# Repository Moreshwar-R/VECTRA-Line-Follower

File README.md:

# 🏁 VECTRA — Line Follower Robot

**ESP32 · TB6612FNG · 10-channel IR array · LSRB intersection logic + Anti-Wobble PID**

VECTRA is a high-speed competition line follower designed to stay locked on the track even when the layout changes from one event to the next. A wide 10-channel IR array reads sharp turns, acute angles and intersections, while decisive LSRB logic layered over a tuned PID controller keeps every junction predictable. Built around an ESP32 and a TB6612FNG driver, it balances speed, stability and fast trackside tuning.

<br>

</div>

---

## ✨ Features

- **Wide 10-sensor coverage** — handles different track layouts without re-wiring.
- **LSRB intersection logic** — Left > Straight > Right priority at junctions.
- **Anti-wobble PID** — dead-band stops shivering on straights, saving time.
- **Line-lost recovery** — remembers last turn direction and sweeps back to the line.
- **Efficient drive** — TB6612FNG H-bridge with N20 micro-gear motors.

---

## 🧩 Components

| Component | Qty | Description |
|-----------|:---:|-------------|
| ESP32 DevKit (30-pin) | 1 | Dual-core microcontroller — reads the sensors and runs the control loop. |
| TB6612FNG motor driver | 1 | Dual H-bridge that drives both motors efficiently and cool. |
| N20 6V micro-gear motor + wheel | 2 | Provides drive; compact and quick. |
| Front caster wheel | 1 | Third contact point for smooth balance. |
| 10-channel reflective IR array | 1 | Senses the line; wide span covers changing track maps. |
| LM2596 buck module | 1 | Steps the 7.4 V battery down to a clean 5 V for the logic. |
| 2S Li-ion battery (7.4 V) | 1 | Main power source. |
| SPST switch | 1 | Master power cut-off. |
| Chassis, standoffs, wires, connectors | — | Frame and interconnections. |

---

## ⚙️ How It Works

1. **Read** the IR array and compute a weighted line `error` (outer sensors pull harder).
2. **Intersections / acute turns (LSRB):** left has priority, straight beats right, sharp turns snap.
3. **Line lost:** spin toward the last known turn until the line is reacquired.
4. **PID steering:** `correction = Kp·error + Kd·(error − lastError)`, applied differentially.

---

## 🛠️ Hardware Design

**Schematic**

<br>

**PCB Layout**

<br>

**3D Model**

</div>

---

## 💾 Firmware & Tuning

- Sketch → [`firmware/line_follower.ino`](firmware/line_follower.ino)
- Board: **ESP32 Dev Module** · Library: **QTRSensors**

| Variable | Default | Role |
|----------|:------:|------|
| `Kp` | 15 | Correction strength |
| `Kd` | 30000 | Damping / overshoot control |
| `baseSpeed` | 250 | Cruise speed (0–255) |
| `THRESHOLD` | 4090 | Black/white cutoff (recalibrate per track) |

---

## 📜 License

- Released under the **MIT License** — see [`LICENSE`](LICENSE).
- Free to use, fork and race.

---

## 🏷️ Topics

`#LineFollower` `#ESP32` `#TB6612FNG` `#PID` `#LSRB` `#Robotics` `#Arduino` `#Embedded` `#KiCad`

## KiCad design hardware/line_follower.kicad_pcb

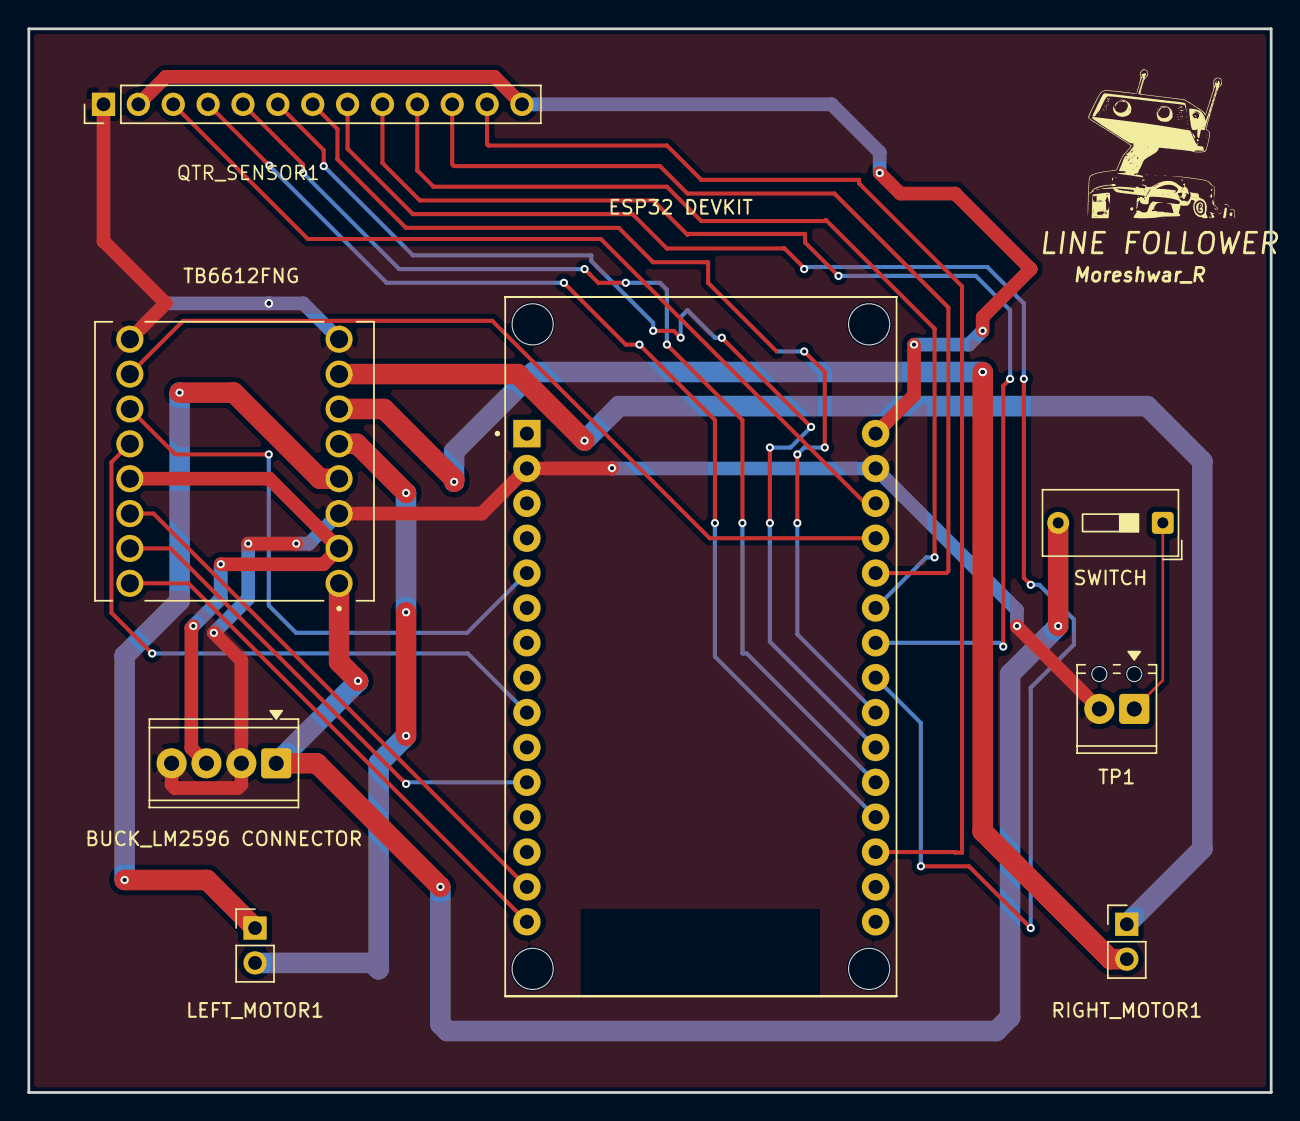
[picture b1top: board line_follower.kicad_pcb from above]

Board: 2 copper layers, 90.5 x 77.5 mm, 8 parts (0 on the bottom side), 24 nets.

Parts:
BUCK_LM2596 CONNECTOR: Conn_01x04_Pin; TerminalBlock_Phoenix_MPT-0,5-4-2.54_1x04_P2.54mm_Horizontal
ESP32 DEVKIT: DEVKIT_V1_ESP32-WROOM-32; MODULE_DEVKIT_V1_ESP32-WROOM-32
LEFT_MOTOR1: Conn_01x02_Pin; PinHeader_1x02_P2.54mm_Vertical
QTR_SENSOR1: Conn_01x13_Pin; PinHeader_1x13_P2.54mm_Vertical
RIGHT_MOTOR1: Conn_01x02_Pin; PinHeader_1x02_P2.54mm_Vertical
SWITCH: SW_SPST; SW_DIP_SPSTx01_Slide_9.78x4.72mm_W7.62mm_P2.54mm
TB6612FNG: TB6612FNG; MODULE_ROB-14450
TP1: TestPoint_2Pole; TerminalBlock_Phoenix_MPT-0,5-2-2.54_1x02_P2.54mm_Horizontal

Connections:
/+5V: BUCK_LM2596 CONNECTOR.3, ESP32 DEVKIT.30 (VIN), QTR_SENSOR1.2, QTR_SENSOR1.13, TB6612FNG.2 (VCC), TB6612FNG.13 (STBY)
/A01: LEFT_MOTOR1.1, TB6612FNG.4 (A01)
/A02: LEFT_MOTOR1.2, TB6612FNG.5 (A02)
/AI1: ESP32 DEVKIT.14 (D22), TB6612FNG.14 (AI1)
/AI2: ESP32 DEVKIT.11 (D21), TB6612FNG.15 (AI2)
/B01: RIGHT_MOTOR1.1, TB6612FNG.7 (B01)
/B02: RIGHT_MOTOR1.2, TB6612FNG.6 (B02)
/BI1: ESP32 DEVKIT.9 (D18), TB6612FNG.12 (BI1)
/BI2: ESP32 DEVKIT.5 (D4), TB6612FNG.11 (BI2)
/D0: ESP32 DEVKIT.18 (VN), QTR_SENSOR1.12
/D1: ESP32 DEVKIT.26 (D14), QTR_SENSOR1.11
/D2: ESP32 DEVKIT.25 (D27), QTR_SENSOR1.10
/D3: ESP32 DEVKIT.24 (D26), QTR_SENSOR1.9
/D4: ESP32 DEVKIT.23 (D25), QTR_SENSOR1.8
/D5: ESP32 DEVKIT.22 (D33), QTR_SENSOR1.7
/D6: ESP32 DEVKIT.21 (D32), QTR_SENSOR1.6
/D7: ESP32 DEVKIT.20 (D35), QTR_SENSOR1.5
/D8: ESP32 DEVKIT.19 (D34), QTR_SENSOR1.4
/D9: ESP32 DEVKIT.28 (D13), QTR_SENSOR1.3
/PWMA: ESP32 DEVKIT.15 (D23), TB6612FNG.16 (PWMA)
/PWMB: ESP32 DEVKIT.27 (D12), TB6612FNG.10 (PWMB)
/VBAT: BUCK_LM2596 CONNECTOR.1, SWITCH.2 (B), TB6612FNG.1 (VM)
GND: BUCK_LM2596 CONNECTOR.2, BUCK_LM2596 CONNECTOR.4, ESP32 DEVKIT.2 (GND), ESP32 DEVKIT.29 (GND), QTR_SENSOR1.1, TB6612FNG.3 (GND), TB6612FNG.8 (GND), TB6612FNG.9 (GND), TP1.2
unnamed: SWITCH.1 (A), TP1.1

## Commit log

2026-06-07 Revise README with comprehensive project details
    Expanded the README to include detailed project overview, features, components, hardware design, firmware, and license information.
2026-06-07 Create LICENSE
